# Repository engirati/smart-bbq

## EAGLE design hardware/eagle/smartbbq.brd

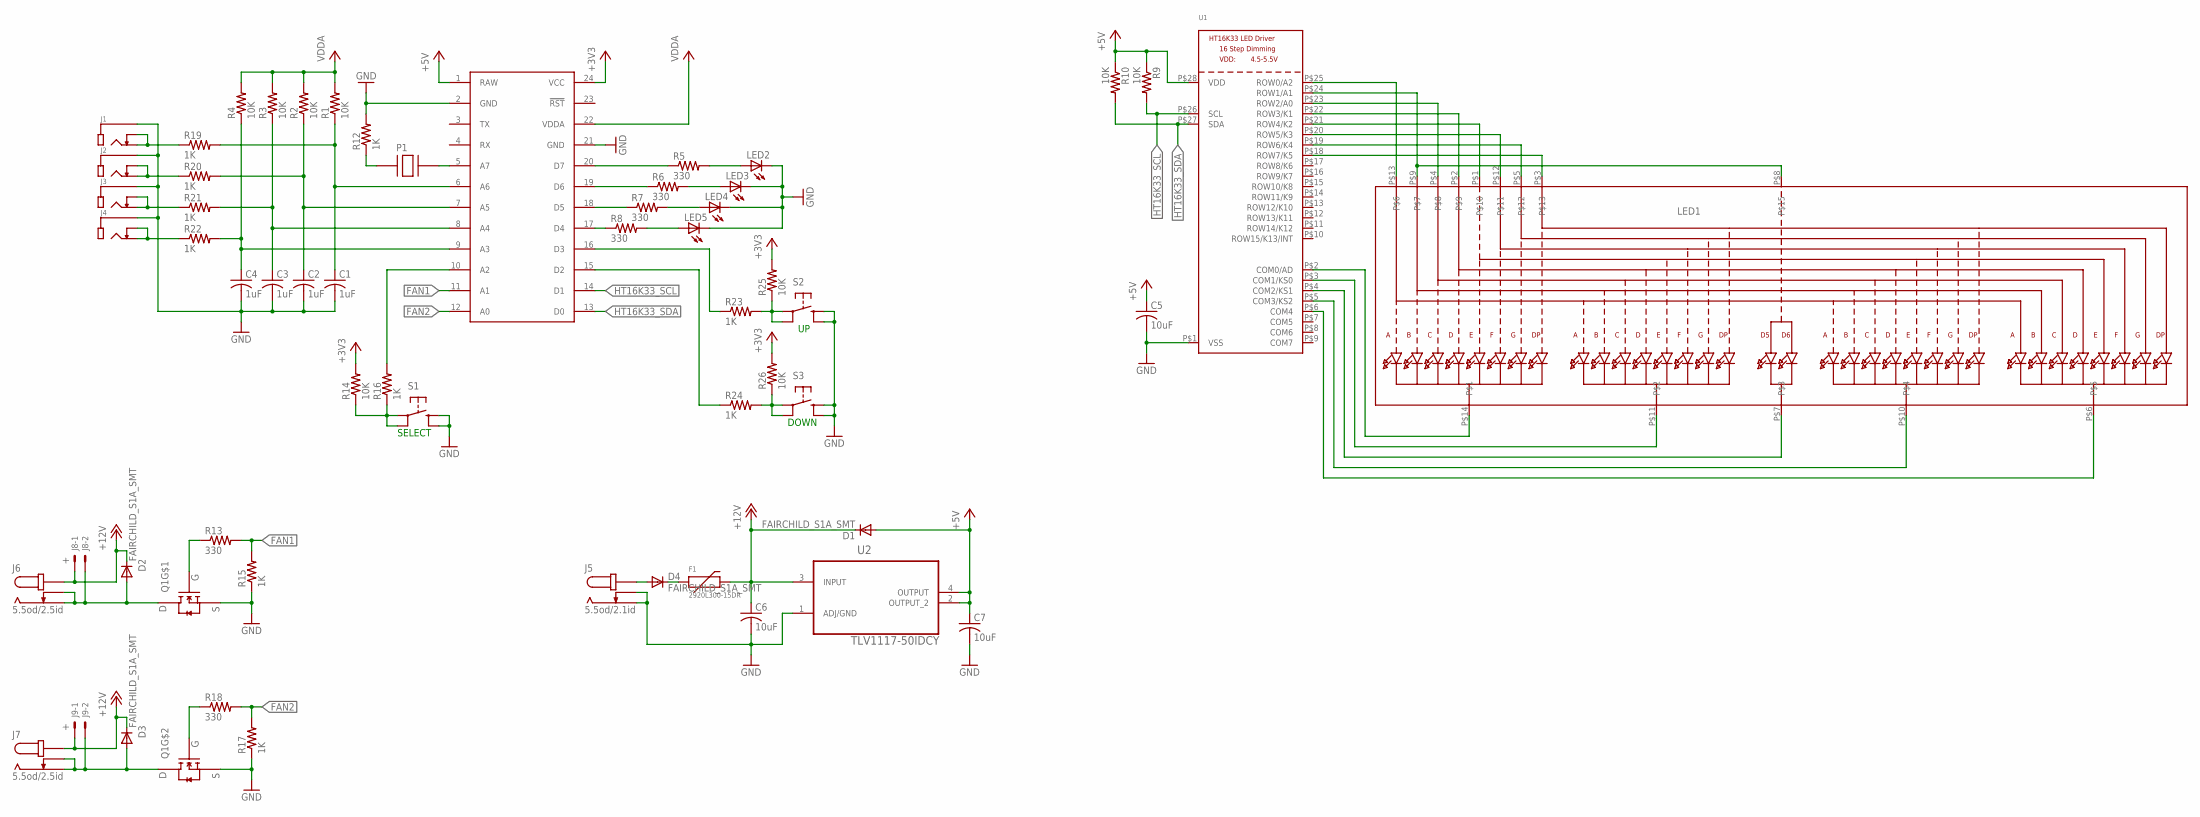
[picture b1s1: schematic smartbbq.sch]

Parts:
C1, C2, C3, C4: 1uF; C0805
C5, C6, C7: 10uF; C0805
D1, D2, D3, D4: FAIRCHILD_S1A_SMT
F1: 2920L300-15DR
J1, J2, J3, J4: MJ_2523_SMT
J5: 5.5od/2.1id; PJ_002AH_SMT
J6, J7: 5.5od/2.5id; PJ_002AH_SMT
J8, J9: +; 7395-02
LED1: DISP_SEGMENT_4DIGIT_BL-Q56C43; SEGMENT-BL-Q56C43
LED2, LED3, LED4, LED5: LEDCHIPLED_0805; CHIPLED_0805
P1: CMT_1603_SMT
Q1: SSM6N58NU
R1, R2, R3, R4, R9, R10, R14, R25, R26: 10K; R0805
R5, R6, R7, R8, R13, R18: 330; R0805
R12, R15, R16, R17, R19, R20, R21, R22, R23, R24: 1K; R0805
S1, S2, S3: PANASONIC-EVQ
SPARK: SPARK_CORECORE; SPARK_CORE
U1: HT16K33_SOP28; SOP28_300MIL
U2: TLV1117-50IDCY; SOT230P700X180-4N

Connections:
+3V3: R14.2, R25.2, R26.2, SPARK.24 (VCC)
+5V: C5.1, C7.1, D1.P$1 (A), R9.1, R10.1, SPARK.1 (RAW), U1.P$28 (VDD), U2.2 (OUTPUT_2), U2.4 (OUTPUT)
+12V: C6.1, D1.P$2 (C), D2.P$2 (C), D3.P$2 (C), F1.P$2, J6.P$1, J6.P$4, J7.P$1, J7.P$4, J8.1, J9.1, U2.3 (INPUT)
A0: LED1.P$4, U1.P$23 (ROW2/A0)
A1: LED1.P$8, LED1.P$9, U1.P$24 (ROW1/A1)
FAN1: R13.2, R15.2, SPARK.11 (A1)
FAN2: R17.2, R18.2, SPARK.12 (A0)
GND: C1.2, C2.2, C3.2, C4.2, C5.2, C6.2, C7.2, J1.P$1, J2.P$1, J3.P$1, J4.P$1, J5.P$2, J5.P$3, LED2.C, LED3.C, LED4.C, LED5.C, Q1.P$1, Q1.P$4, R12.2, R15.1, R17.1, S1.P$3 (3), S1.P$4 (4), S2.P$3 (3), S2.P$4 (4), S3.P$3 (3), S3.P$4 (4), SPARK.2 (GND), SPARK.21 (GND), U1.P$1 (VSS), U2.1 (ADJ/GND)
HT16K33_SCL: R9.2, SPARK.14 (D1), U1.P$26 (SCL)
HT16K33_SDA: R10.2, SPARK.13 (D0), U1.P$27 (SDA)
unnamed: LED1.P$14, U1.P$2 (COM0/AD)
unnamed: LED1.P$11, U1.P$3 (COM1/KS0)
unnamed: LED1.P$10, U1.P$5 (COM3/KS2)
unnamed: LED1.P$7, U1.P$4 (COM2/KS1)
unnamed: R8.1, SPARK.17 (D4)
unnamed: R7.1, SPARK.18 (D5)
unnamed: R6.1, SPARK.19 (D6)
unnamed: R5.1, SPARK.20 (D7)
unnamed: LED2.A, R5.2
unnamed: LED3.A, R6.2
unnamed: LED4.A, R7.2
unnamed: LED5.A, R8.2
unnamed: R24.1, SPARK.15 (D2)
unnamed: R23.1, SPARK.16 (D3)
unnamed: C1.1, R1.1, R19.2, SPARK.6 (A6)
unnamed: R16.2, SPARK.10 (A2)
unnamed: C2.1, R2.1, R20.2, SPARK.7 (A5)
unnamed: C3.1, R3.1, R21.2, SPARK.8 (A4)
unnamed: C4.1, R4.1, R22.2, SPARK.9 (A3)
unnamed: LED1.P$12, U1.P$20 (ROW5/K3)
unnamed: LED1.P$5, U1.P$19 (ROW6/K4)
unnamed: LED1.P$6, U1.P$6 (COM4)
unnamed: LED1.P$2, U1.P$22 (ROW3/K1)
unnamed: LED1.P$1, U1.P$21 (ROW4/K2)
unnamed: LED1.P$13, U1.P$25 (ROW0/A2)
unnamed: LED1.P$3, U1.P$18 (ROW7/K5)
unnamed: P1.P$1, R12.1
unnamed: P1.P$2, SPARK.5 (A7)
unnamed: D3.P$1 (A), J7.P$2, J7.P$3, J9.2, Q1.P$3
unnamed: Q1.P$5, R18.1
unnamed: D2.P$1 (A), J6.P$2, J6.P$3, J8.2, Q1.P$6
unnamed: D4.P$2 (C), F1.P$1
unnamed: Q1.P$2, R13.1
unnamed: R14.1, R16.1, S1.P$1 (1), S1.P$2 (2)
unnamed: J4.P$2, J4.P$3, R22.1
unnamed: J3.P$2, J3.P$3, R21.1
unnamed: J2.P$2, J2.P$3, R20.1
unnamed: J1.P$2, J1.P$3, R19.1
unnamed: R23.2, R25.1, S2.P$1 (1), S2.P$2 (2)
unnamed: D4.P$1 (A), J5.P$1, J5.P$4
unnamed: R24.2, R26.1, S3.P$1 (1), S3.P$2 (2)
VCC: R1.2, R2.2, R3.2, R4.2, SPARK.22 (VDDA)

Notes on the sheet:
DOWN
SELECT

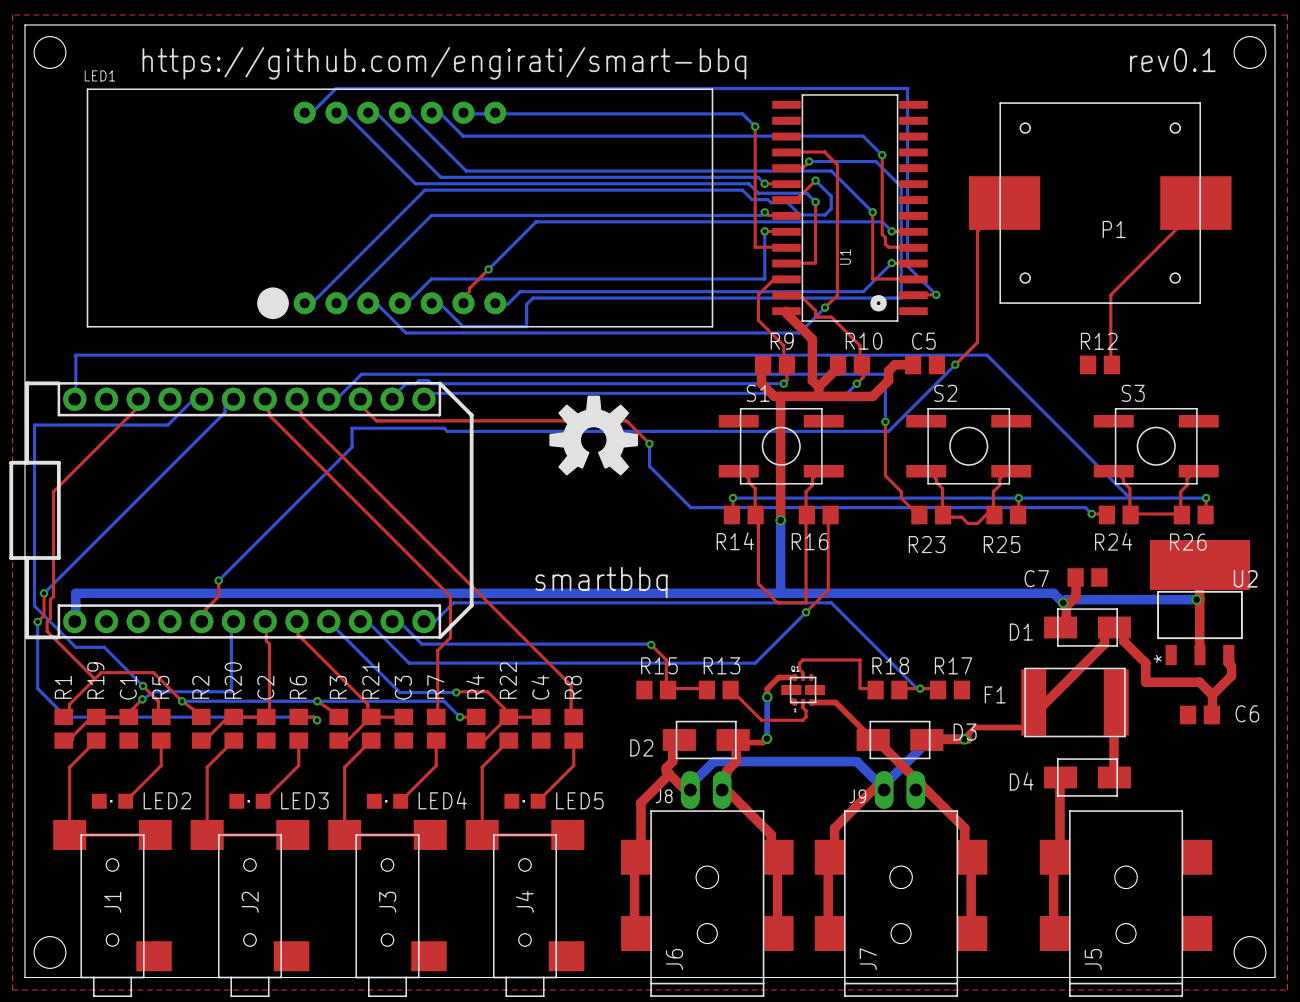
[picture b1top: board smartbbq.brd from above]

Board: 2 copper layers, 100.0 x 76.2 mm, 60 parts (0 on the bottom side), 52 nets.

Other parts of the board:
U$1: OSHW-LOGO-L

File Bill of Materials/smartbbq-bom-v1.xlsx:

Qty | Value | Device | Package | Parts | Description | Manufacturer | Manufacturer P/N | Supplier | Supplier P/N
1 |  | DISP_SEGMENT_4DIGIT_BL-Q56C43 | SEGMENT-BL-Q56C43 | LED1 |  | Luckylight | KW4-56NXLB-P | Adafruit | 865
1 |  | HT16K33_SOP28 | SOP28_300MIL | U1 |  | Holtek | HT16K33 | Keyan Technology Co.,Ltd | 1240179945
4 |  | LEDCHIPLED_0805 | CHIPLED_0805 | LED2, LED3, LED4, LED5 | LED | Lite-On Inc | LTST-C171KRKT | Digi-Key | 160-1427-1-ND
3 |  | PANASONIC-EVQ | PANASONIC-EVQ | S1,S2, S3 |  | Panasonic | EVQ-Q2K03W | Digi-Key | P12943SCT-ND
2 | + | 22-05-7028-02 | 7395-02 | J8, J9 | CONNECTOR | 3M | 961102-6404-AR | Digi-Key | 3M9447-ND
9 | 10K | R-US_R0805 | R0805 | R1, R2, R3, R4, R9, R10, R14, R25, R26 | RESISTOR, American symbol | Yageo | RC0805JR-0710KL | Digi-Key | 311-10KARCT-ND
3 | 10uF | C-USC0805 | C0805 | C5, C6, C7 | CAPACITOR, American symbol | Samsung Electro-Mechanics America, Inc | CL21A106KOQNNNE | Digi-Key | 1276-1096-1-ND
10 | 1K | R-US_R0805 | R0805 | R12, R15, R16, R17, R19, R20, R21, R22, R23, R24 | RESISTOR, American symbol | Yageo | RC0805JR-071KL | Digi-Key | 311-1.0KARCT-ND
4 | 1uF | C-USC0805 | C0805 | C1, C2, C3, C4 | CAPACITOR, American symbol | Samsung Electro-Mechanics America, Inc | CL21B105KAFNNNE | Digi-Key | 1276-1066-1-ND
1 | 2920L300-15DR | 2920L300-15DR | 2920L300-15DR | F1 |  | Littelfuse Inc | 2920L300/15DR | Digi-Key | F2875CT-ND
6 | 330 | R-US_R0805 | R0805 | R5, R6, R7, R8, R13, R18 | RESISTOR, American symbol | Yageo | RC0805JR-07330RL | Digi-Key | 311-330ARCT-ND
1 | 5.5od/2.1id | PJ_002AH_SMT | PJ_002AH_SMT | J5 | MODEL: PJ-002AH-SMT or PJ-002BH-SMT | CUI Inc | PJ-002AH-SMT-TR | Digi-Key | CP-002AHPJCT-ND
2 | 5.5od/2.5id | PJ_002AH_SMT | PJ_002AH_SMT | J6, J7 | MODEL: PJ-002AH-SMT or PJ-002BH-SMT | CUI Inc | PJ-002BH-SMT-TR | Digi-Key | CP-002BHPJCT-ND
1 | CMT_1603_SMT | CMT_1603_SMT | CMT_1603_SMT | P1 |  | CUI Inc | CMT-1603-SMT-TR | Digi-Key | 102-1193-2-ND
4 | FAIRCHILD_S1A_SMT | FAIRCHILD_S1A_SMT | FAIRCHILD_S1A_SMT | D1, D2, D3, D4 |  | Fairchild Semiconductor | S1A | Digi-Key | S1AFSCT-ND
4 | MJ_2523_SMT | MJ_2523_SMT | MJ_2523_SMT | J1, J2, J3, J4 |  | CUI Inc | MJ-2523-SMT | Digi-Key | CP-2523MJCT-ND
1 | SPARK_CORECORE | SPARK_CORECORE | SPARK_CORE | SPARK |  | Spark |  | Spark
1 | SSM6N58NU | SSM6N58NU | SSM6N58NU | Q1 |  | Toshiba Semiconductor and Storage | SSM6N58NU,LF | Digi-Key | SSM6N58NULFCT-ND
1 | TLV1117-50IDCY | TLV1117-33IDCY | SOT230P700X180-4N | U2 | V REG, LDO, 3.3V, 0.8A | Texas Instruments | TLV1117-50IDCYR | Digi-Key | 296-21115-1-ND

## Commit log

2014-06-08 Initial firmware and schematic
2014-06-10 LCD & driver
    LCD, driver, values added and various other updates.
2014-06-11 Piezo addition
2014-06-16 Fans, power, misc
    Added fan output and power circuitry. Cleaned up a few random things.
    Swapped 0603 parts for 0805.
2014-06-19 Change fan driver circuitry
    Updated fan driver circuitry to use single MOSFET.
2014-06-23 Multiple updates. See description.
    Looks good! I will suggest a few things though:
    1.Probe inputs looks like maybe 2.5 or 3.5mm jacks. Connect the TIP to
    the analog input, and the SLEEVE or RING to GND. That way ESD has a
    harder path into you Spark Core inputs.
    I connected the tip and NC switch to analog in and the sleeve to gnd.
    2.It might be a good idea to do a Low Pass RC filter with the inputs in
2014-06-24 Added resistors and tweaked values
    Added missing select switch resistors and changed probe input resistor
    values.
2014-06-28 PCB added
    PCB added and a few schematic tweaks
2014-07-01 rev0.1 of board
    rev0.1 of board and minor schematic edits
2014-07-01 Heatsink pads added
    Added larger pads to act as a heatsink for voltage regulator and mosfet.
2014-07-02 Datasheets and bom
2014-08-13 PID & bugs
    Addition of PID hard coded to temp alarm on probe 4 for testing. Added
    alarm logic when up/down buttons are pressed. Created API variables.
    Fixed thermistor bug and display bug.
2014-08-13 Missed a file
    Missed SmartProbe.cpp last commit

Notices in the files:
parts and their libraries:
SparkFun-Aesthetics: Licensing: Creative Commons ShareAlike 4.0 International - https://creativecommons.org/licenses/by-sa/4.0
